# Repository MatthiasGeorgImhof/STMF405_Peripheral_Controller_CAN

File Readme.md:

Periphery contronller based F405 for ardupilot AP_Periph

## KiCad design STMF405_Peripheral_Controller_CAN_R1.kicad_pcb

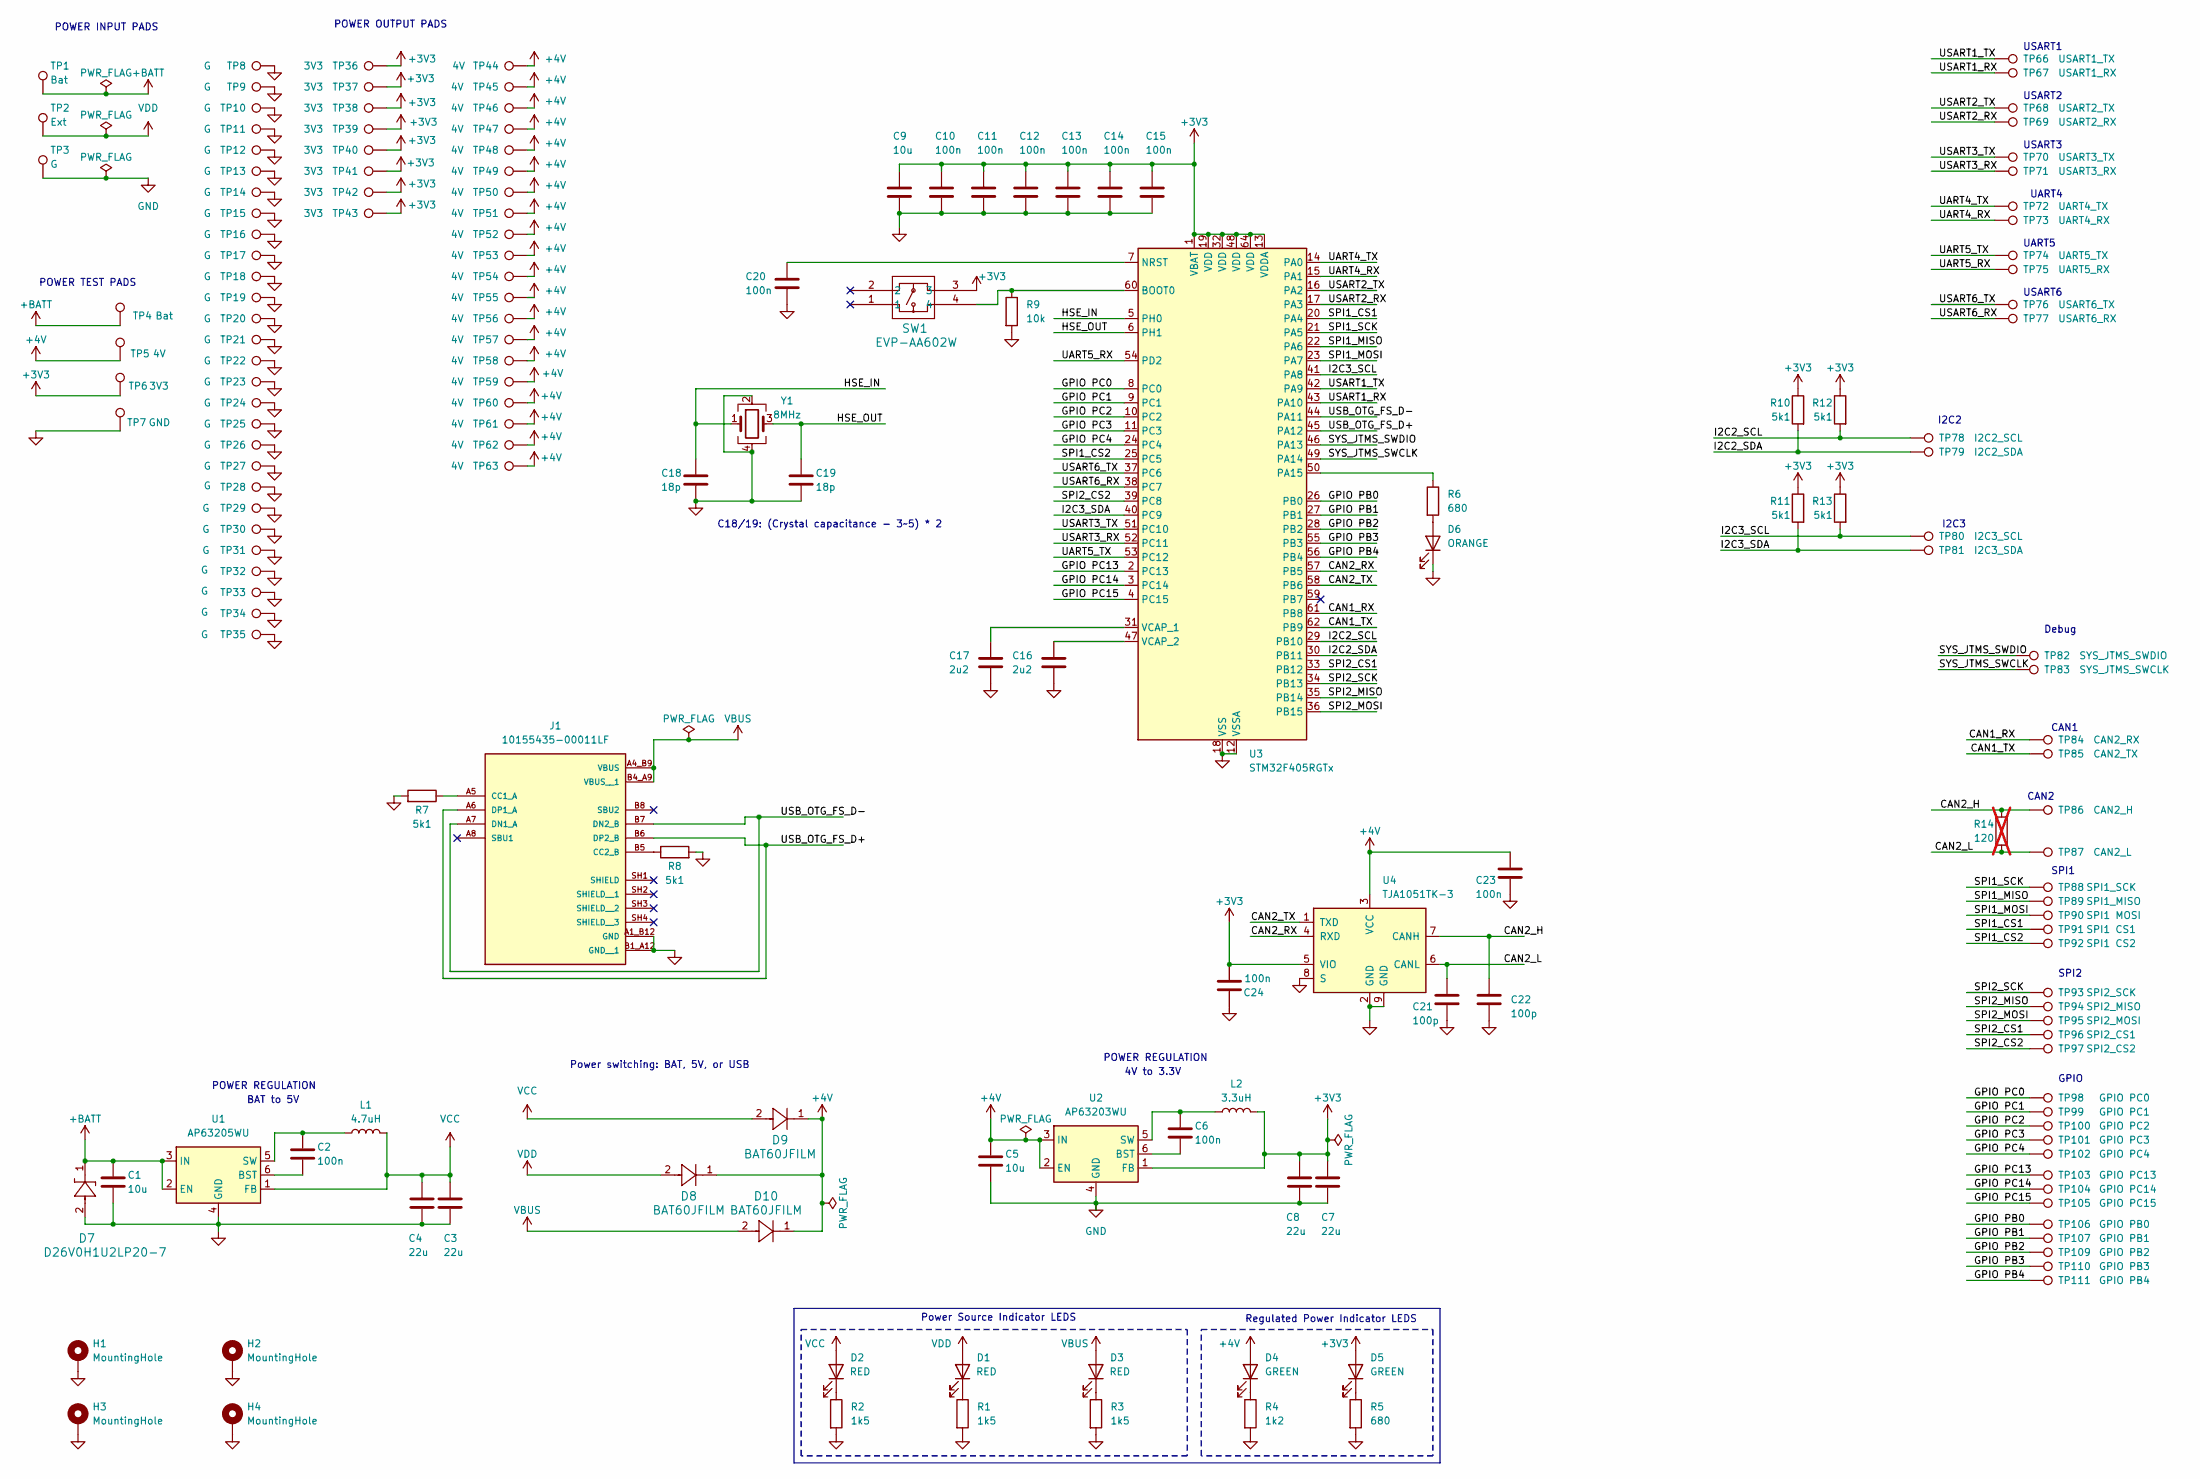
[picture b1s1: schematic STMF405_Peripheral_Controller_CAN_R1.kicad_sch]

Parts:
C1, C5: 10u; C_0805_2012Metric; Voltage 50; Part Number GRM21BR61H106KE43L
C2, C6, C10, C11, C12, C13, C14, C15, C20, C23, C24: 100n; C_0402_1005Metric; Voltage 16; Part Number CC0402KRX5R7BB104
C3, C4, C7, C8: 22u; C_0805_2012Metric; Voltage 25; Part Number CC0805MKX5R8BB226
C9: 10u; C_0603_1608Metric; Voltage 16; Part Number GRM188R61C106MA73D
C16, C17: 2u2; C_0402_1005Metric; Voltage 16; Part Number GRM155R61C225KE11D
C18, C19: 18p; C_0402_1005Metric; Voltage 16; Tolerance 1%; Part Number CC0402FRNPO9BN180
C21, C22: 100p; C_0402_1005Metric; Voltage 16; Tolerance 1%; Part Number CC0402FRNPO9BN101
D1, D2, D3: RED; LED_0603_1608Metric; Part Number LTST-C191KRKT
D4, D5: GREEN; LED_0603_1608Metric; Part Number LTST-C191GKT
D6: ORANGE; LED_0603_1608Metric; Part Number LTST-C191KFKT
D7: D26V0H1U2LP20-7; U-DFN2020-2_DIO; Part Number D26V0H1U2LP20-7
D8, D9, D10: BAT60JFILM; D_SOD-323F; Part Number BAT60JFILM
H1, H2, H3, H4: MountingHole; MountingHole_4.3mm_M4_Pad_Via_Custom
J1: 10155435-00011LF; AMPHENOL_10155435-00011LF; PARTREV C
L1: 4.7uH; IND_DFE322520FD-4R7M=P2_MUR; Part Number DFE322520FD-4R7M=P2
L2: 3.3uH; IND_DFE322520FD-4R7M=P2_MUR; Part Number DFE322512F-3R3M=P2
R1, R2, R3: 1k5; R_0402_1005Metric; Part Number RC0402FR-071K5L
R4: 1k2; R_0402_1005Metric; Part Number RC0402FR-071K2L
R5, R6: 680; R_0402_1005Metric; Part Number RC0402FR-07680RL
R7, R8, R10, R11, R12, R13: 5k1; R_0402_1005Metric; Part Number RC0402FR-075K1L
R9: 10k; R_0402_1005Metric; Part Number RC0402FR-0710KL
R14: 120; R_0805_2012Metric; Part Number RT0805FRE07120RL; not fitted
SW1: EVP-AA602W; EVPAA602; Part Number EVP-AA602W
TP1, TP4: Bat; TestPoint_Pad_2.0x2.0mm
TP2: Ext; TestPoint_Pad_2.0x2.0mm
TP3: G; TestPoint_Pad_2.0x2.0mm
TP5: 4V; TestPoint_Pad_2.0x2.0mm
TP6: 3V3; TestPoint_Pad_2.0x2.0mm
TP7: GND; TestPoint_Pad_2.0x2.0mm
TP8, TP9, TP10, TP11, TP12, TP13, TP14, TP15, TP16, TP17, TP18, TP19, TP20, TP21, TP22, TP23, TP24, TP25, TP26, TP27, TP28, TP29, TP30, TP31, TP32, TP33, TP34, TP35: G; TestPoint_Pad_1.0x1.5mm
TP36, TP37, TP38, TP39, TP40, TP41, TP42, TP43: 3V3; TestPoint_Pad_1.0x1.5mm
TP44, TP45, TP46, TP47, TP48, TP49, TP50, TP51, TP52, TP53, TP54, TP55, TP56, TP57, TP58, TP59, TP60, TP61, TP62, TP63: 4V; TestPoint_Pad_1.0x1.5mm
TP66: USART1_TX; TestPoint_Pad_1.0x1.5mm
TP67: USART1_RX; TestPoint_Pad_1.0x1.5mm
TP68: USART2_TX; TestPoint_Pad_1.0x1.5mm
TP69: USART2_RX; TestPoint_Pad_1.0x1.5mm
TP70: USART3_TX; TestPoint_Pad_1.0x1.5mm
TP71: USART3_RX; TestPoint_Pad_1.0x1.5mm
TP72: UART4_TX; TestPoint_Pad_1.0x1.5mm
TP73: UART4_RX; TestPoint_Pad_1.0x1.5mm
TP74: UART5_TX; TestPoint_Pad_1.0x1.5mm
TP75: UART5_RX; TestPoint_Pad_1.0x1.5mm
TP76: USART6_TX; TestPoint_Pad_1.0x1.5mm
TP77: USART6_RX; TestPoint_Pad_1.0x1.5mm
TP78: I2C2_SCL; TestPoint_Pad_1.0x1.5mm
TP79: I2C2_SDA; TestPoint_Pad_1.0x1.5mm
TP80: I2C3_SCL; TestPoint_Pad_1.0x1.5mm
TP81: I2C3_SDA; TestPoint_Pad_1.0x1.5mm
TP82: SYS_JTMS_SWDIO; TestPoint_Pad_1.0x1.5mm
TP83: SYS_JTMS_SWCLK; TestPoint_Pad_1.0x1.5mm
TP84: CAN2_RX; TestPoint_Pad_1.0x1.5mm
TP85: CAN2_TX; TestPoint_Pad_1.0x1.5mm
TP86: CAN2_H; TestPoint_Pad_1.0x1.5mm
TP87: CAN2_L; TestPoint_Pad_1.0x1.5mm
TP88: SPI1_SCK; TestPoint_Pad_1.0x1.5mm
TP89: SPI1_MISO; TestPoint_Pad_1.0x1.5mm
TP90: SPI1 MOSI; TestPoint_Pad_1.0x1.5mm
TP91: SPI1 CS1; TestPoint_Pad_1.0x1.5mm
TP92: SPI1 CS2; TestPoint_Pad_1.0x1.5mm
TP93: SPI2_SCK; TestPoint_Pad_1.0x1.5mm
TP94: SPI2_MISO; TestPoint_Pad_1.0x1.5mm
TP95: SPI2_MOSI; TestPoint_Pad_1.0x1.5mm
TP96: SPI2_CS1; TestPoint_Pad_1.0x1.5mm
TP97: SPI2_CS2; TestPoint_Pad_1.0x1.5mm
TP98: GPIO PC0; TestPoint_Pad_1.0x1.5mm
TP99: GPIO PC1; TestPoint_Pad_1.0x1.5mm
TP100: GPIO PC2; TestPoint_Pad_1.0x1.5mm
TP101: GPIO PC3; TestPoint_Pad_1.0x1.5mm
TP102: GPIO PC4; TestPoint_Pad_1.0x1.5mm
TP103: GPIO PC13; TestPoint_Pad_1.0x1.5mm
TP104: GPIO PC14; TestPoint_Pad_1.0x1.5mm
TP105: GPIO PC15; TestPoint_Pad_1.0x1.5mm
TP106: GPIO PB0; TestPoint_Pad_1.0x1.5mm
TP107: GPIO PB1; TestPoint_Pad_1.0x1.5mm
TP109: GPIO PB2; TestPoint_Pad_1.0x1.5mm
TP110: GPIO PB3; TestPoint_Pad_1.0x1.5mm
TP111: GPIO PB4; TestPoint_Pad_1.0x1.5mm
U1: AP63205WU; TSOT-23-6; Part Number AP63205WU-7
U2: AP63203WU; TSOT-23-6; Part Number AP63203WU-7
U3: STM32F405RGTx; LQFP-64_10x10mm_P0.5mm; Part Number STM32F405RGT6
U4: TJA1051TK-3; DFN-8-1EP_3x3mm_P0.65mm_EP1.55x2.4mm; Part Number TJA1051TK/3,118
Y1: 8MHz; Crystal_SMD_3225-4Pin_3.2x2.5mm; Part Number ECS-80-12-33-JGN-TR

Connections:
+3V3: C7.1, C8.1, C9.1, C10.1, C11.1, C12.1, C13.1, C14.1, C15.1, C24.2, D5.2 (A), L2.2, R10.1, R11.1, R12.1, R13.1, SW1.3, TP6.1, TP36.1, TP37.1, TP38.1, TP39.1, TP40.1, TP41.1, TP42.1, TP43.1, U2.1 (FB), U3.1 (VBAT), U3.13 (VDDA), U3.19 (VDD), U3.32 (VDD), U3.48 (VDD), U3.64 (VDD), U4.5 (VIO)
+4V: C5.1, C23.1, D4.2 (A), D8.1, D9.1, D10.1, TP5.1, TP44.1, TP45.1, TP46.1, TP47.1, TP48.1, TP49.1, TP50.1, TP51.1, TP52.1, TP53.1, TP54.1, TP55.1, TP56.1, TP57.1, TP58.1, TP59.1, TP60.1, TP61.1, TP62.1, TP63.1, U2.2 (EN), U2.3 (IN), U4.3 (VCC)
+BATT: C1.1, D7.1, TP1.1, TP4.1, U1.2 (EN), U1.3 (IN)
/CAN1_RX: TP84.1, U3.61 (PB8)
/CAN1_TX: TP85.1, U3.62 (PB9)
/CAN2_H: C22.1, R14.1, TP86.1, U4.7 (CANH)
/CAN2_L: C21.1, R14.2, TP87.1, U4.6 (CANL)
/CAN2_RX: U3.57 (PB5), U4.4 (RXD)
/CAN2_TX: U3.58 (PB6), U4.1 (TXD)
/GPIO PB0: TP106.1, U3.26 (PB0)
/GPIO PB1: TP107.1, U3.27 (PB1)
/GPIO PB2: TP109.1, U3.28 (PB2)
/GPIO PB3: TP110.1, U3.55 (PB3)
/GPIO PB4: TP111.1, U3.56 (PB4)
/GPIO PC0: TP98.1, U3.8 (PC0)
/GPIO PC1: TP99.1, U3.9 (PC1)
/GPIO PC2: TP100.1, U3.10 (PC2)
/GPIO PC3: TP101.1, U3.11 (PC3)
/GPIO PC4: TP102.1, U3.24 (PC4)
/GPIO PC13: TP103.1, U3.2 (PC13)
/GPIO PC14: TP104.1, U3.3 (PC14)
/GPIO PC15: TP105.1, U3.4 (PC15)
/HSE_IN: C18.1, U3.5 (PH0), Y1.1
/HSE_OUT: C19.1, U3.6 (PH1), Y1.3
/I2C2_SCL: R12.2, TP78.1, U3.29 (PB10)
/I2C2_SDA: R10.2, TP79.1, U3.30 (PB11)
/I2C3_SCL: R13.2, TP80.1, U3.41 (PA8)
/I2C3_SDA: R11.2, TP81.1, U3.40 (PC9)
/SPI1_CS1: TP91.1, U3.20 (PA4)
/SPI1_CS2: TP92.1, U3.25 (PC5)
/SPI1_MISO: TP89.1, U3.22 (PA6)
/SPI1_MOSI: TP90.1, U3.23 (PA7)
/SPI1_SCK: TP88.1, U3.21 (PA5)
/SPI2_CS1: TP96.1, U3.33 (PB12)
/SPI2_CS2: TP97.1, U3.39 (PC8)
/SPI2_MISO: TP94.1, U3.35 (PB14)
/SPI2_MOSI: TP95.1, U3.36 (PB15)
/SPI2_SCK: TP93.1, U3.34 (PB13)
/SYS_JTMS_SWCLK: TP83.1, U3.49 (PA14)
/SYS_JTMS_SWDIO: TP82.1, U3.46 (PA13)
/UART4_RX: TP73.1, U3.15 (PA1)
/UART4_TX: TP72.1, U3.14 (PA0)
/UART5_RX: TP75.1, U3.54 (PD2)
/UART5_TX: TP74.1, U3.53 (PC12)
/USART1_RX: TP67.1, U3.43 (PA10)
/USART1_TX: TP66.1, U3.42 (PA9)
/USART2_RX: TP69.1, U3.17 (PA3)
/USART2_TX: TP68.1, U3.16 (PA2)
/USART3_RX: TP71.1, U3.52 (PC11)
/USART3_TX: TP70.1, U3.51 (PC10)
/USART6_RX: TP77.1, U3.38 (PC7)
/USART6_TX: TP76.1, U3.37 (PC6)
/USB_OTG_FS_D+: J1.A6 (DP1_A), J1.B6 (DP2_B), U3.45 (PA12)
/USB_OTG_FS_D-: J1.A7 (DN1_A), J1.B7 (DN2_B), U3.44 (PA11)
GND: C1.2, C3.2, C4.2, C5.2, C7.2, C8.2, C9.2, C10.2, C11.2, C12.2, C13.2, C14.2, C15.2, C16.2, C17.2, C18.2, C19.2, C20.2, C21.2, C22.2, C23.2, C24.1, D6.1 (K), D7.2, H1.1, H2.1, H3.1, H4.1, J1.A1_B12 (GND), J1.B1_A12 (GND__1), R1.2, R2.2, R3.2, R4.2, R5.2, R7.2, R8.2, R9.2, TP3.1, TP7.1, TP8.1, TP9.1, TP10.1, TP11.1, TP12.1, TP13.1, TP14.1, TP15.1, TP16.1, TP17.1, TP18.1, TP19.1, TP20.1, TP21.1, TP22.1, TP23.1, TP24.1, TP25.1, TP26.1, TP27.1, TP28.1, TP29.1, TP30.1, TP31.1, TP32.1, TP33.1, TP34.1, TP35.1, U1.4 (GND), U2.4 (GND), U3.12 (VSSA), U3.18 (VSS), U3.63 (VSS), U4.2 (GND), U4.8 (S), U4.9 (GND), Y1.2, Y1.4
unnamed: D1.1 (K), R1.1
unnamed: D2.1 (K), R2.1
unnamed: D3.1 (K), R3.1
unnamed: D4.1 (K), R4.1
unnamed: D5.1 (K), R5.1
unnamed: D6.2 (A), R6.2
unnamed: J1.A5 (CC1_A), R7.1
unnamed: J1.B5 (CC2_B), R8.1
unnamed: C2.2, U1.6 (BST)
unnamed: C2.1, L1.1, U1.5 (SW)
unnamed: C6.2, U2.6 (BST)
unnamed: C6.1, L2.1, U2.5 (SW)
unnamed: R9.1, SW1.4, U3.60 (BOOT0)
unnamed: C20.1, U3.7 (NRST)
unnamed: R6.1, U3.50 (PA15)
unnamed: C17.1, U3.31 (VCAP_1)
unnamed: C16.1, U3.47 (VCAP_2)
VBUS: D3.2 (A), D10.2, J1.A4_B9 (VBUS), J1.B4_A9 (VBUS__1)
VCC: C3.1, C4.1, D2.2 (A), D9.2, L1.2, U1.1 (FB)
VDD: D1.2 (A), D8.2, TP2.1

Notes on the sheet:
UART4
GPIO
4V to 3.3V
POWER OUTPUT PADS
Debug
Power switching: BAT, 5V, or USB
Power Source Indicator LEDS
CAN1
POWER REGULATION
BAT to 5V
UART5
I2C3
POWER TEST PADS
USART2
SPI2
SPI1
USART3
POWER INPUT PADS
I2C2
USART6
C18/19: (Crystal capacitance - 3~5) * 2
USART1
CAN2
Regulated Power Indicator LEDS

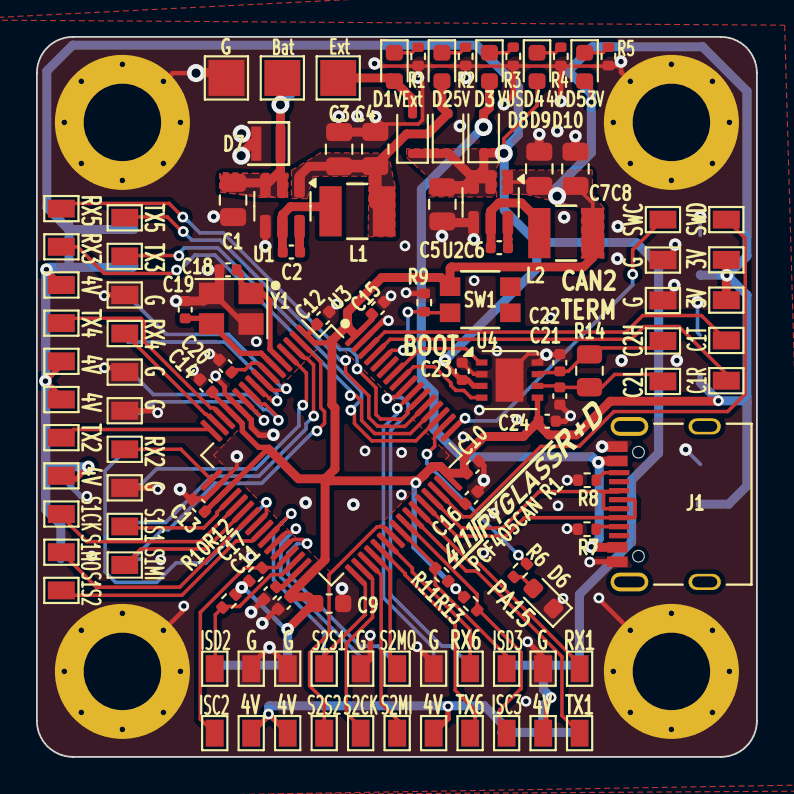
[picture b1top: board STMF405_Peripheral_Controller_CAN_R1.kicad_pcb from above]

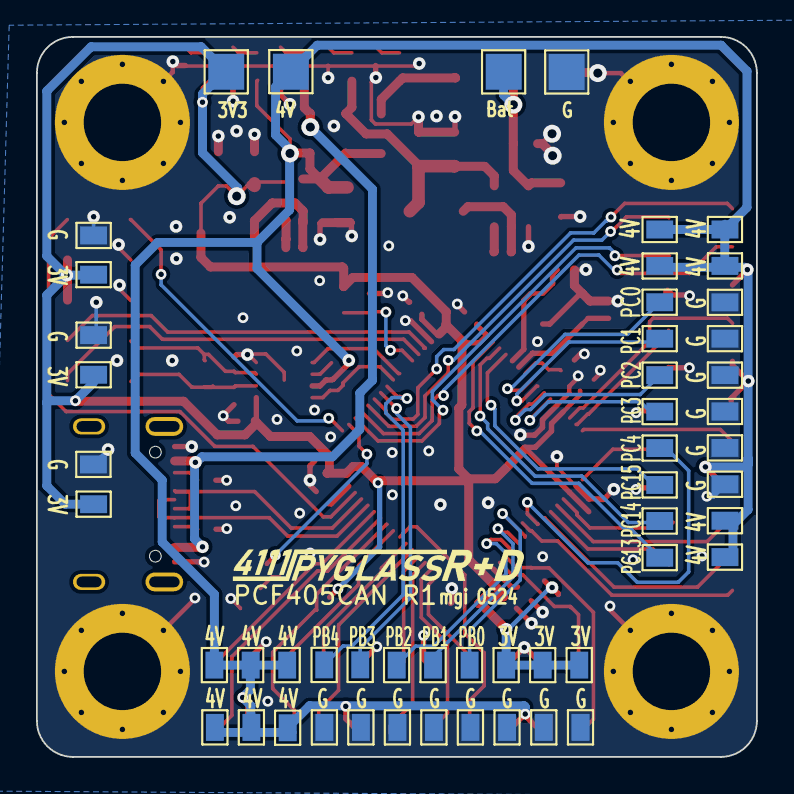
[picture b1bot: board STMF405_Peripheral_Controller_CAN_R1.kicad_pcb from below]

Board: 2 copper layers, 40.0 x 40.0 mm, 169 parts (52 on the bottom side), 75 nets.

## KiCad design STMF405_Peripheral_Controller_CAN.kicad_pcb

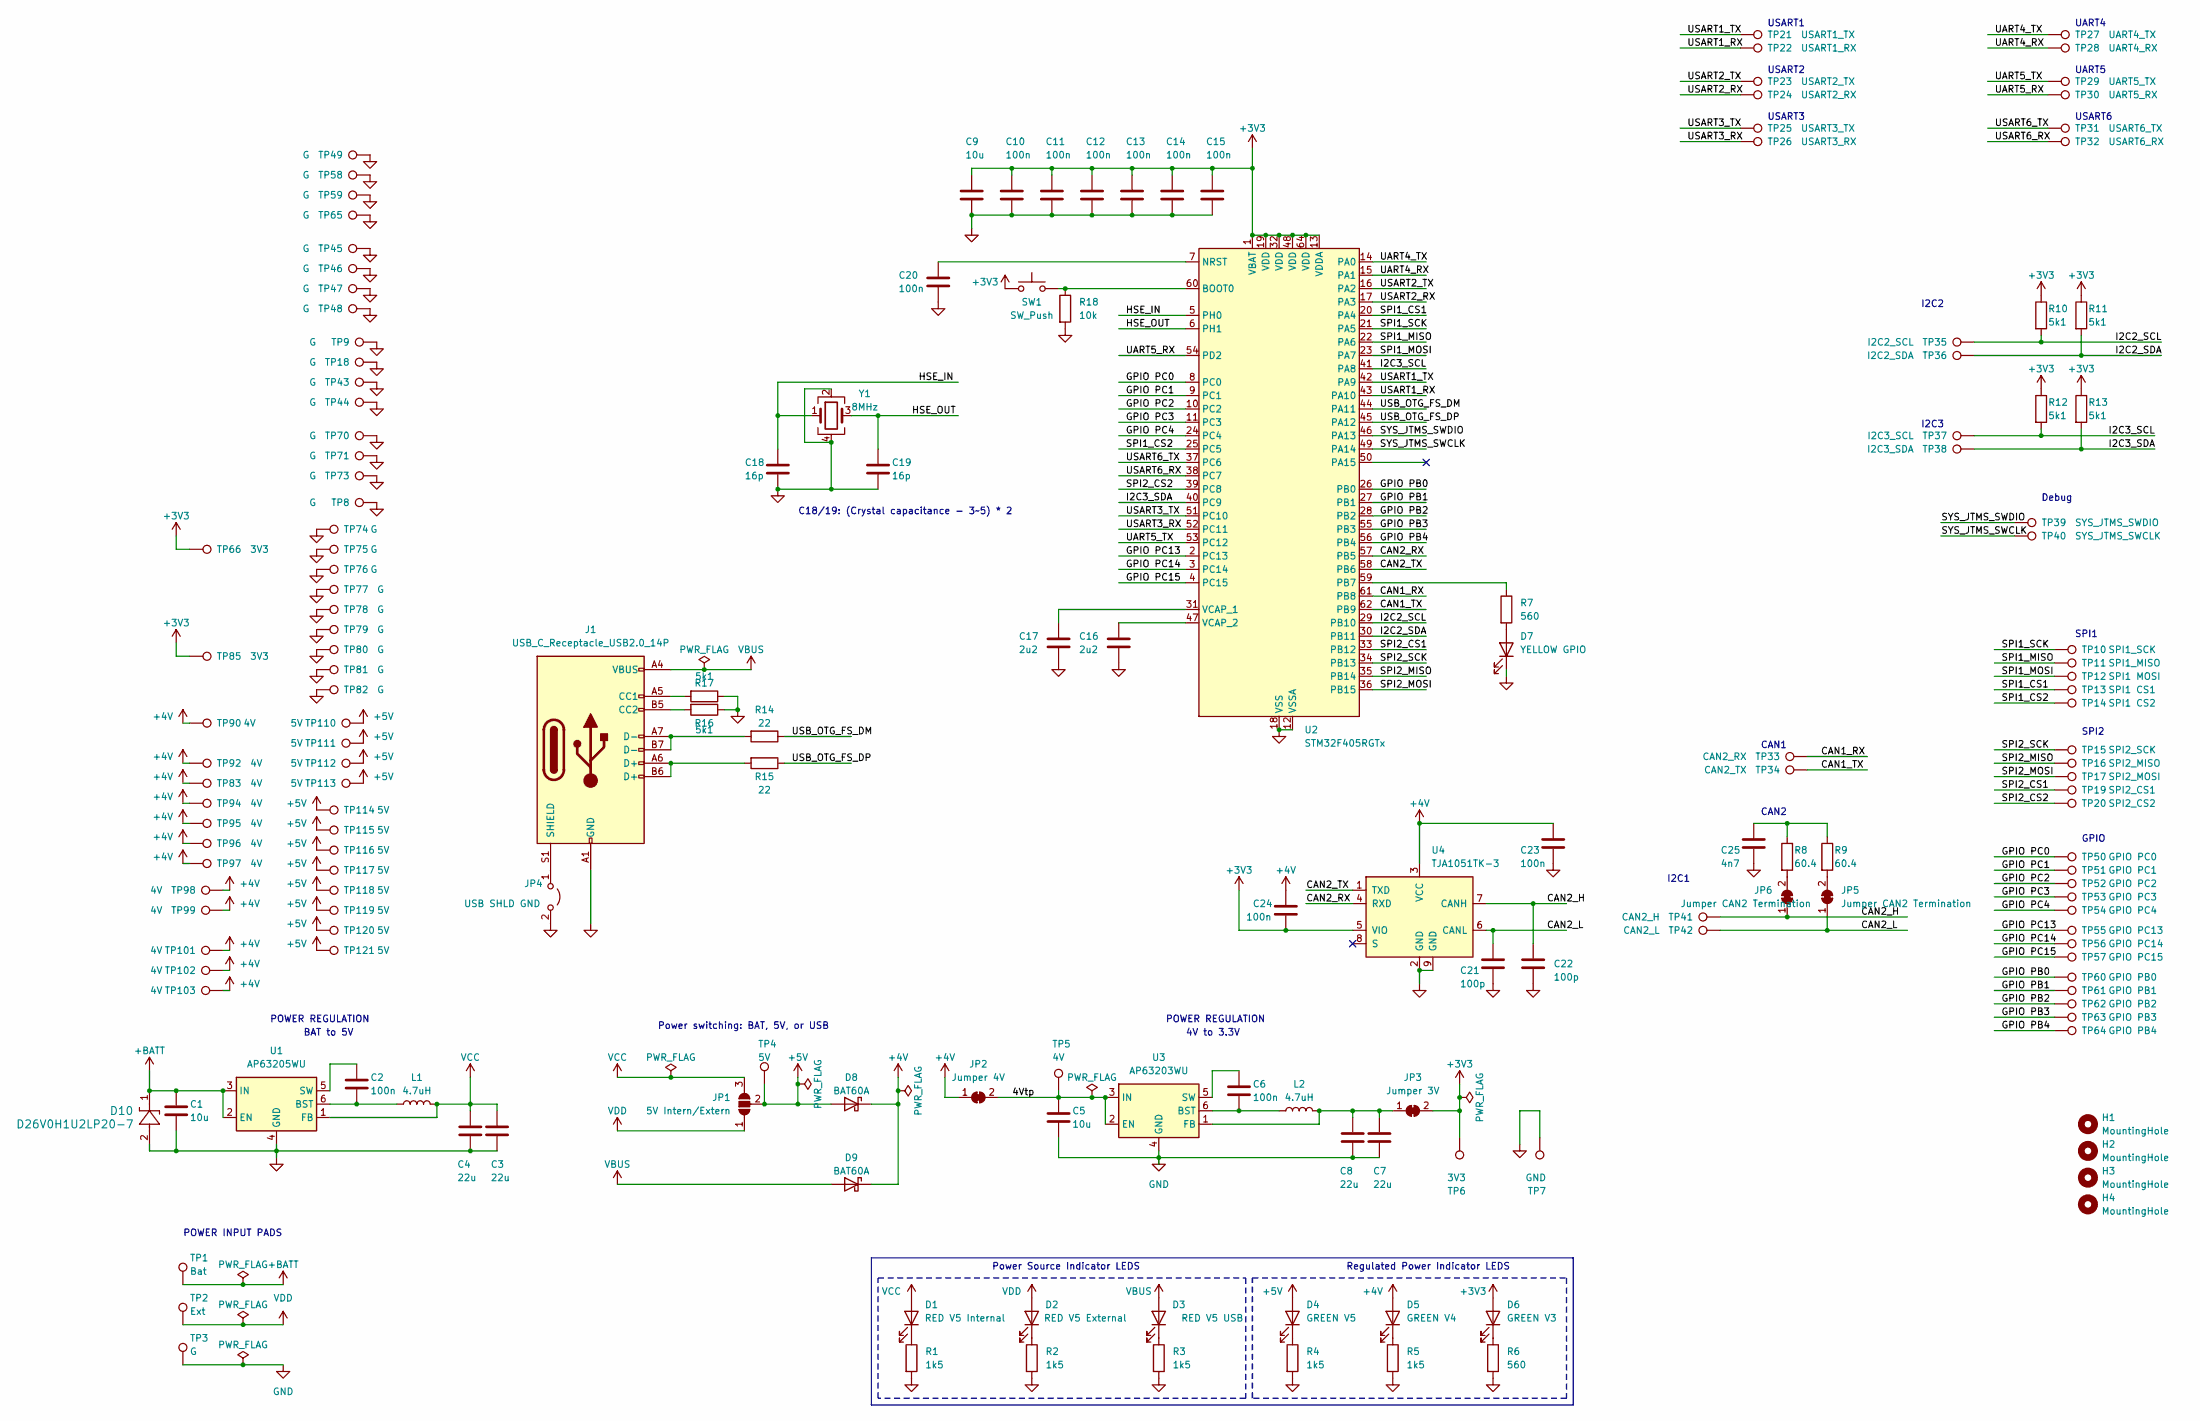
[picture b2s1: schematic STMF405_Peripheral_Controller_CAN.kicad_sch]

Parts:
C1, C5: 10u; C_0805_2012Metric; Voltage 50; Part Number GRM21BR61H106KE43L
C2, C6, C10, C11, C12, C13, C14, C15, C20, C23, C24: 100n; C_0402_1005Metric; Voltage 16; Part Number CC0402KRX7R7BB104
C3, C4, C7, C8: 22u; C_0805_2012Metric; Voltage 25; Part Number CL21A226MAYNNNE
C9: 10u; C_0603_1608Metric; Voltage 16; Part Number CL10X106MO8NRNC
C16, C17: 2u2; C_0402_1005Metric; Voltage 16; Part Number GRM155R61C225KE11D
C18, C19: 16p; C_0402_1005Metric; Voltage 16; Part Number CC0402JPNPO9BN160
C21, C22: 100p; C_0402_1005Metric; Voltage 16; Part Number CC0402KRX7R7BB101
C25: 4n7; C_0402_1005Metric; Voltage 16; Part Number CC0402KRX7R8BB472
D1: RED V5 Internal; LED_0603_1608Metric; Part Number LTST-C191KRKT
D2: RED V5 External; LED_0603_1608Metric; Part Number LTST-C191KRKT
D3: RED V5 USB; LED_0603_1608Metric; Part Number LTST-C191KRKT
D4: GREEN V5; LED_0603_1608Metric; Part Number LTST-C190GKT
D5: GREEN V4; LED_0603_1608Metric; Part Number LTST-C190GKT
D6: GREEN V3; LED_0603_1608Metric; Part Number LTST-C190GKT
D7: YELLOW GPIO; LED_0603_1608Metric; Part Number LTST-C191KFKT
D8, D9: BAT60A; D_SOD-323; Voltage 10; Part Number BAT60AE6327HTSA1
D10: D26V0H1U2LP20-7; U-DFN2020-2_DIO; Voltage 26; Part Number D26V0H1U2LP20-7
H1, H2, H3, H4: MountingHole; MountingHole_4.3mm_M4_DIN965_Pad
J1: USB_C_Receptacle_USB2.0_14P; USB_C_Receptacle_Amphenol_12401610E4-2A; Part Number 12401610E4#2A
JP1: 5V Intern/Extern; SolderJumper-3_P1.3mm_Open_Pad1.0x1.5mm
JP2: Jumper 4V; SolderJumper-2_P1.3mm_Bridged_Pad1.0x1.5mm
JP3: Jumper 3V; SolderJumper-2_P1.3mm_Bridged_Pad1.0x1.5mm
JP4: USB SHLD GND; SolderJumper-2_P1.3mm_Open_Pad1.0x1.5mm
JP5, JP6: Jumper CAN2 Termination; SolderJumper-2_P1.3mm_Bridged_Pad1.0x1.5mm
L1, L2: 4.7uH; L_0603_1608Metric; Part Number SDFL1608Q4R7KTF
R1, R2, R3, R4, R5: 1k5; R_0402_1005Metric; Part Number RC0402FR-071K5L
R6, R7: 560; R_0402_1005Metric; Part Number RC0402FR-07560RL
R8, R9: 60.4; R_0402_1005Metric; Part Number RC0402FR-0760R4L
R10, R11, R12, R13, R16, R17: 5k1; R_0402_1005Metric; Part Number RC0402FR-075K1L
R14, R15: 22; R_0402_1005Metric; Part Number RC0402FR-0722RL
R18: 10k; R_0402_1005Metric; Part Number RC0402FR-0710KL
SW1: SW_Push; SW_SPST_EVQPE1; Part Number EVQPE104K
TP1: Bat; TestPoint_Pad_2.0x2.0mm
TP2: Ext; TestPoint_Pad_2.0x2.0mm
TP3: G; TestPoint_Pad_2.0x2.0mm
TP4: 5V; TestPoint_Pad_2.0x2.0mm
TP5: 4V; TestPoint_Pad_2.0x2.0mm
TP6: 3V3; TestPoint_Pad_2.0x2.0mm
TP7: GND; TestPoint_Pad_2.0x2.0mm
TP8, TP9, TP18, TP43, TP44, TP45, TP46, TP47, TP48, TP49, TP58, TP59, TP65, TP70, TP71, TP73, TP74, TP75, TP76, TP77, TP78, TP79, TP80, TP81, TP82: G; TestPoint_Pad_1.0x1.5mm
TP10: SPI1_SCK; TestPoint_Pad_1.0x1.5mm
TP11: SPI1_MISO; TestPoint_Pad_1.0x1.5mm
TP12: SPI1 MOSI; TestPoint_Pad_1.0x1.5mm
TP13: SPI1 CS1; TestPoint_Pad_1.0x1.5mm
TP14: SPI1 CS2; TestPoint_Pad_1.0x1.5mm
TP15: SPI2_SCK; TestPoint_Pad_1.0x1.5mm
TP16: SPI2_MISO; TestPoint_Pad_1.0x1.5mm
TP17: SPI2_MOSI; TestPoint_Pad_1.0x1.5mm
TP19: SPI2_CS1; TestPoint_Pad_1.0x1.5mm
TP20: SPI2_CS2; TestPoint_Pad_1.0x1.5mm
TP21: USART1_TX; TestPoint_Pad_1.0x1.5mm
TP22: USART1_RX; TestPoint_Pad_1.0x1.5mm
TP23: USART2_TX; TestPoint_Pad_1.0x1.5mm
TP24: USART2_RX; TestPoint_Pad_1.0x1.5mm
TP25: USART3_TX; TestPoint_Pad_1.0x1.5mm
TP26: USART3_RX; TestPoint_Pad_1.0x1.5mm
TP27: UART4_TX; TestPoint_Pad_1.0x1.5mm
TP28: UART4_RX; TestPoint_Pad_1.0x1.5mm
TP29: UART5_TX; TestPoint_Pad_1.0x1.5mm
TP30: UART5_RX; TestPoint_Pad_1.0x1.5mm
TP31: USART6_TX; TestPoint_Pad_1.0x1.5mm
TP32: USART6_RX; TestPoint_Pad_1.0x1.5mm
TP33: CAN2_RX; TestPoint_Pad_1.0x1.5mm
TP34: CAN2_TX; TestPoint_Pad_1.0x1.5mm
TP35: I2C2_SCL; TestPoint_Pad_1.0x1.5mm
TP36: I2C2_SDA; TestPoint_Pad_1.0x1.5mm
TP37: I2C3_SCL; TestPoint_Pad_1.0x1.5mm
TP38: I2C3_SDA; TestPoint_Pad_1.0x1.5mm
TP39: SYS_JTMS_SWDIO; TestPoint_Pad_1.0x1.5mm
TP40: SYS_JTMS_SWCLK; TestPoint_Pad_1.0x1.5mm
TP41: CAN2_H; TestPoint_Pad_1.0x1.5mm
TP42: CAN2_L; TestPoint_Pad_1.0x1.5mm
TP50: GPIO PC0; TestPoint_Pad_1.0x1.5mm
TP51: GPIO PC1; TestPoint_Pad_1.0x1.5mm
TP52: GPIO PC2; TestPoint_Pad_1.0x1.5mm
TP53: GPIO PC3; TestPoint_Pad_1.0x1.5mm
TP54: GPIO PC4; TestPoint_Pad_1.0x1.5mm
TP55: GPIO PC13; TestPoint_Pad_1.0x1.5mm
TP56: GPIO PC14; TestPoint_Pad_1.0x1.5mm
TP57: GPIO PC15; TestPoint_Pad_1.0x1.5mm
TP60: GPIO PB0; TestPoint_Pad_1.0x1.5mm
TP61: GPIO PB1; TestPoint_Pad_1.0x1.5mm
TP62: GPIO PB2; TestPoint_Pad_1.0x1.5mm
TP63: GPIO PB3; TestPoint_Pad_1.0x1.5mm
TP64: GPIO PB4; TestPoint_Pad_1.0x1.5mm
TP66, TP85: 3V3; TestPoint_Pad_1.0x1.5mm
TP83, TP90, TP92, TP94, TP95, TP96, TP97, TP98, TP99, TP101, TP102, TP103: 4V; TestPoint_Pad_1.0x1.5mm
TP110, TP111, TP112, TP113, TP114, TP115, TP116, TP117, TP118, TP119, TP120, TP121: 5V; TestPoint_Pad_1.0x1.5mm
U1: AP63205WU; TSOT-23-6; Part Number AP63205WU-7
U2: STM32F405RGTx; LQFP-64_10x10mm_P0.5mm; Part Number STM32F405RGT6
U3: AP63203WU; TSOT-23-6; Part Number AP63203WU-7
U4: TJA1051TK-3; DFN-8-1EP_3x3mm_P0.65mm_EP1.55x2.4mm; Part Number TJA1051TK/3,118
Y1: 8MHz; Crystal_SMD_3225-4Pin_3.2x2.5mm; Part Number ECS-80-12-33-JGN-TR

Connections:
+3V3: C9.1, C10.1, C11.1, C12.1, C13.1, C14.1, C15.1, C24.2, D6.2 (A), JP3.2 (B), R10.1, R11.1, R12.1, R13.1, SW1.2, TP6.1, TP66.1, TP85.1, U2.1 (VBAT), U2.13 (VDDA), U2.19 (VDD), U2.32 (VDD), U2.48 (VDD), U2.64 (VDD), U4.5 (VIO)
+4V: C23.1, C24.1, D5.2 (A), D8.1 (K), D9.1 (K), JP2.1 (A), TP83.1, TP90.1, TP92.1, TP94.1, TP95.1, TP96.1, TP97.1, TP98.1, TP99.1, TP101.1, TP102.1, TP103.1, U4.3 (VCC)
+5V: D4.2 (A), D8.2 (A), JP1.2 (C), TP4.1, TP110.1, TP111.1, TP112.1, TP113.1, TP114.1, TP115.1, TP116.1, TP117.1, TP118.1, TP119.1, TP120.1, TP121.1
+BATT: C1.1, D10.1, TP1.1, U1.2 (EN), U1.3 (IN)
/4Vtp: C5.1, JP2.2 (B), TP5.1, U3.2 (EN), U3.3 (IN)
/CAN1_RX: TP33.1, U2.61 (PB8)
/CAN1_TX: TP34.1, U2.62 (PB9)
/CAN2_H: C22.1, JP6.1 (A), TP41.1, U4.7 (CANH)
/CAN2_L: C21.1, JP5.1 (A), TP42.1, U4.6 (CANL)
/CAN2_RX: U2.57 (PB5), U4.4 (RXD)
/CAN2_TX: U2.58 (PB6), U4.1 (TXD)
/GPIO PB0: TP60.1, U2.26 (PB0)
/GPIO PB1: TP61.1, U2.27 (PB1)
/GPIO PB2: TP62.1, U2.28 (PB2)
/GPIO PB3: TP63.1, U2.55 (PB3)
/GPIO PB4: TP64.1, U2.56 (PB4)
/GPIO PC0: TP50.1, U2.8 (PC0)
/GPIO PC1: TP51.1, U2.9 (PC1)
/GPIO PC2: TP52.1, U2.10 (PC2)
/GPIO PC3: TP53.1, U2.11 (PC3)
/GPIO PC4: TP54.1, U2.24 (PC4)
/GPIO PC13: TP55.1, U2.2 (PC13)
/GPIO PC14: TP56.1, U2.3 (PC14)
/GPIO PC15: TP57.1, U2.4 (PC15)
/HSE_IN: C18.1, U2.5 (PH0), Y1.1
/HSE_OUT: C19.1, U2.6 (PH1), Y1.3
/I2C2_SCL: R10.2, TP35.1, U2.29 (PB10)
/I2C2_SDA: R11.2, TP36.1, U2.30 (PB11)
/I2C3_SCL: R12.2, TP37.1, U2.41 (PA8)
/I2C3_SDA: R13.2, TP38.1, U2.40 (PC9)
/SPI1_CS1: TP13.1, U2.20 (PA4)
/SPI1_CS2: TP14.1, U2.25 (PC5)
/SPI1_MISO: TP11.1, U2.22 (PA6)
/SPI1_MOSI: TP12.1, U2.23 (PA7)
/SPI1_SCK: TP10.1, U2.21 (PA5)
/SPI2_CS1: TP19.1, U2.33 (PB12)
/SPI2_CS2: TP20.1, U2.39 (PC8)
/SPI2_MISO: TP16.1, U2.35 (PB14)
/SPI2_MOSI: TP17.1, U2.36 (PB15)
/SPI2_SCK: TP15.1, U2.34 (PB13)
/SYS_JTMS_SWCLK: TP40.1, U2.49 (PA14)
/SYS_JTMS_SWDIO: TP39.1, U2.46 (PA13)
/UART4_RX: TP28.1, U2.15 (PA1)
/UART4_TX: TP27.1, U2.14 (PA0)
/UART5_RX: TP30.1, U2.54 (PD2)
/UART5_TX: TP29.1, U2.53 (PC12)
/USART1_RX: TP22.1, U2.43 (PA10)
/USART1_TX: TP21.1, U2.42 (PA9)
/USART2_RX: TP24.1, U2.17 (PA3)
/USART2_TX: TP23.1, U2.16 (PA2)
/USART3_RX: TP26.1, U2.52 (PC11)
/USART3_TX: TP25.1, U2.51 (PC10)
/USART6_RX: TP32.1, U2.38 (PC7)
/USART6_TX: TP31.1, U2.37 (PC6)
/USB_OTG_FS_DM: R14.1, U2.44 (PA11)
/USB_OTG_FS_DP: R15.1, U2.45 (PA12)
GND: C1.2, C3.2, C4.2, C5.2, C7.2, C8.2, C9.2, C10.2, C11.2, C12.2, C13.2, C14.2, C15.2, C16.2, C17.2, C18.2, C19.2, C20.2, C21.2, C22.2, C23.2, C25.2, D7.1 (K), D10.2, J1.A1 (GND), J1.A12 (GND), J1.B1 (GND), J1.B12 (GND), JP4.2 (B), R1.2, R2.2, R3.2, R4.2, R5.2, R6.2, R16.1, R17.1, R18.2, TP3.1, TP7.1, TP8.1, TP9.1, TP18.1, TP43.1, TP44.1, TP45.1, TP46.1, TP47.1, TP48.1, TP49.1, TP58.1, TP59.1, TP65.1, TP70.1, TP71.1, TP73.1, TP74.1, TP75.1, TP76.1, TP77.1, TP78.1, TP79.1, TP80.1, TP81.1, TP82.1, U1.4 (GND), U2.12 (VSSA), U2.18 (VSS), U2.63 (VSS), U3.4 (GND), U4.2 (GND), U4.9 (GND), Y1.2, Y1.4
unnamed: C25.1, R8.1, R9.1
unnamed: D1.1 (K), R1.1
unnamed: D2.1 (K), R2.1
unnamed: D3.1 (K), R3.1
unnamed: D4.1 (K), R4.1
unnamed: D5.1 (K), R5.1
unnamed: D6.1 (K), R6.1
unnamed: D7.2 (A), R7.2
unnamed: J1.A5 (CC1), R17.2
unnamed: J1.B5 (CC2), R16.2
unnamed: J1.A6 (D+), J1.B6 (D+), R15.2
unnamed: J1.A7 (D-), J1.B7 (D-), R14.2
unnamed: J1.S1 (SHIELD), JP4.1 (A)
unnamed: C7.1, C8.1, JP3.1 (A), L2.2, U3.1 (FB)
unnamed: JP5.2 (B), R9.2
unnamed: JP6.2 (B), R8.2
unnamed: C2.2, L1.1, U1.6 (BST)
unnamed: C2.1, U1.5 (SW)
unnamed: R18.1, SW1.1, U2.60 (BOOT0)
unnamed: C20.1, U2.7 (NRST)
unnamed: R7.1, U2.59 (PB7)
unnamed: C17.1, U2.31 (VCAP_1)
unnamed: C16.1, U2.47 (VCAP_2)
unnamed: C6.2, L2.1, U3.6 (BST)
unnamed: C6.1, U3.5 (SW)
VBUS: D3.2 (A), D9.2 (A), J1.A4 (VBUS), J1.A9 (VBUS), J1.B4 (VBUS), J1.B9 (VBUS)
VCC: C3.1, C4.1, D1.2 (A), JP1.3 (B), L1.2, U1.1 (FB)
VDD: D2.2 (A), JP1.1 (A), TP2.1

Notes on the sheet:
UART4
GPIO
4V to 3.3V
Debug
Power switching: BAT, 5V, or USB
Power Source Indicator LEDS
CAN1
POWER REGULATION
I2C1
BAT to 5V
UART5
I2C3
USART2
SPI2
SPI1
USART3
POWER INPUT PADS
I2C2
USART6
C18/19: (Crystal capacitance - 3~5) * 2
USART1
CAN2
Regulated Power Indicator LEDS

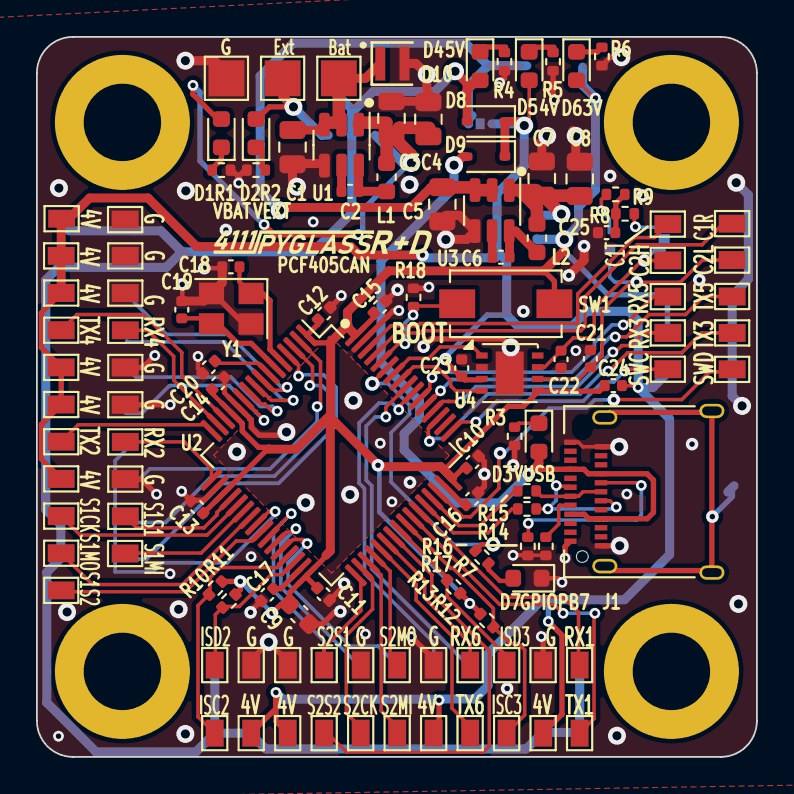
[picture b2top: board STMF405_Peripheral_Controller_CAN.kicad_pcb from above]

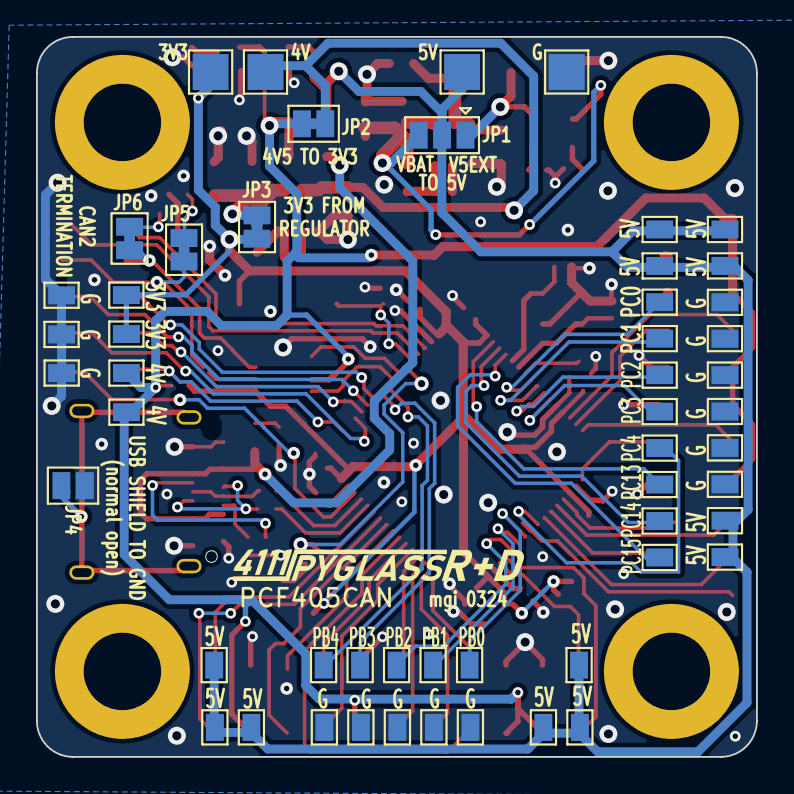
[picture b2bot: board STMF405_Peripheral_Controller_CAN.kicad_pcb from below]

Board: 2 copper layers, 40.0 x 40.0 mm, 175 parts (53 on the bottom side), 85 nets.

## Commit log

2024-07-21 setup project
2024-07-21 checking first fabricated release
2024-07-21 some addional files
2024-07-21 corrected power supply and streamlined traces
2024-07-21 cleanup resistors for LEDs, check rules and layout
2024-07-21 move step files to step3d folder
